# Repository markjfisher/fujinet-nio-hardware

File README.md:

# fujinet-nio-hardware
Hardware projects for NIO

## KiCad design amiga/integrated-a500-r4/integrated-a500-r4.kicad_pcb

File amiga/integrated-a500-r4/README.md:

Current integration checkpoint: [CadMust-Neo plan and compatibility findings](review/cadmust-integration/plan.md). Approved capacitor footprints and obsolete groups are now repaired; no optimisation or placement movement has run.

# A500 R4 — first physical placement candidate

R4 turns the protected R3 circuit into a **111 × 117 mm horizontal sidecar
placement**, with the female A500 socket at the right edge and an 18 mm
component-free band behind that edge (the socket solder lands are excepted). It is a new project;
released passive hardware and R0–R3 remain unchanged.

Placement preparation: [readiness report, exact bulk capacitors and lock classifications](review/placement-readiness/report.md). Q5 library warning is resolved; PCB positions/locks are unchanged.

Current status: [Phase 1 implementation and checks](review/component-optimisation/phase1-status.md).
Open the [native project](integrated-a500-r4.kicad_pro), [current schematic](review/schematic.pdf)
or [board and staging preview](phase1/board-and-staging.png). There are **199 fitted
components and four mounting holes**. New/repackaged components are staged outside
the preserved outline, awaiting placement. **There is no routed copper.** Earlier
placement pictures and review inventories are historical baseline artifacts.
USB main power is mandatory; the [implemented protection](review/component-optimisation/bus-output-disable-proposal.md)
uses a small current-limited host-interface supply and supervises all relevant rails.

The following table records the original placement basis; Phase 1 supersedes its
power/guard description and component counts.

| Requirement | Implementation | Evidence/check | Remaining decision or check |
| --- | --- | --- | --- |
| Direct horizontal A500 attachment | ED86BGFBK assembly footprint at right edge; board extends left | Original Matze Eagle package and supplied Gerbers; native check of all 86 pads | Tail-forming process, socket/body and case fit |
| Run / Flash RP / Flash ESP | Shared USB-C, two analog switches, cold mode jumper | Eight control combinations; exact native nets | Coupled USB routing and switched-circuit qualification |
| Independent recovery | Four physical BOOT/RESET buttons; RP SWD and ESP UART headers | Complete pin allocation and PCB pad coverage | Final button/header height and enclosure access |
| Power and Amiga-off isolation | USB-C >=1.5A source; protected input, reverse blocking; Amiga 5V sensed only | [Power calculation and assumptions](../integrated-a500-r3/power-review.md); 1.166A conditional input budget | Buck layout, effective capacitance, thermal/fault/current-downgrade behaviour |
| RP pins and bus safety | All 48 GPIO allocated; dedicated USB/QSPI/debug; LVC buffers and hardware interlocks | [Pin table](rp2350-pin-allocation.csv); 65,536 static and 65,536 sequential cases | PIO deadlines, propagation delay and active-bus validation |
| RP regulator placement | Six reference footprints and relative positions from Raspberry Pi's R4 design | Native geometric/net checks; source hash and MIT notice retained | Copper, ground return and regulator qualification |
| Physical layout | Four copper layers enabled; local bus/control bypass capacitors; antenna keepout on all copper | Native parity, DRC, pad mapping and visual inspection | Stackup, critical routing, ordinary routing, final BOM and DFM |

The electrical decisions remain in the [R3 power review](../integrated-a500-r3/power-review.md),
[R2 engineering](../integrated-a500-r2/engineering.md) and
[bus review](../integrated-a500-r3/bus-review.md). R4 changes footprint assignments
and makes the unused microSD detection contacts explicit; it does not change
the bus protocol or consume additional RP GPIO. Existing USB demonstrations
and passive logic-analyzer observations remain accepted.

See [mechanical/component evidence](implementation.md) and
[verification and outstanding findings](review/verification.md).
The circuit BOM is not yet an orderable manufacturing BOM. No fabrication
files, vendor upload, order, push or workspace submodule-pin change is included.

## Historical construction — do not rerun on the authoritative project

The scripts below reconstruct the obsolete baseline and would discard incremental
Phase 1 changes and manual placement. Native KiCad is now authoritative. The
[Phase 1 tooling](phase1/README.md) is a one-time migration record, not a board generator.

Source the workspace `scripts/env.sh`. Run `build.py`, `pcb_build.py`,
`finish_mcp.py` and `apply_bypass.py` with the pinned
`repos/fujinet-nio-hardware/.local-tools/kicad/venv/bin/python`.
Run the native checking/geometry scripts with system Python:

1. `make_footprints.py` constructs the A500 footprint through pcbnew. The six
   checked-in RP footprints are already present. To refresh those, download the
   cited official reference ZIP and pass its extracted directory to
   `import_rp_footprints.py`.
2. Register the project-local library using
   `uv run --with kiutils==1.4.8 python register_library.py`.
   This writes library configuration only, using its LibTable serializer.
3. `build.py`, then `check.py`: MCP schematic construction and independent
   native netlist/ERC/PDF export. `update_footprints.py` is an optional incremental
   property update, not required after a fresh build.
4. `pcb_build.py`: MCP board construction and constrained placement. Its
   `pending_approval` status is an internal routing checkpoint, not a request
   for another user permission.
5. `finish_native.py`, then `finish_mcp.py`: repair the documented tool export
   gaps, establish DFM targets and make the placement adjustments.
6. `plan_bypass.py`, then `apply_bypass.py`: calculate legal local bypass
   positions and apply them through MCP.
7. `fit_mechanics.py`, then `apply_mechanics.py`, then `reserve_connector.py`
   applies the owner-measured envelope without regenerating the board.
8. `plan_clusters.py`, then MCP `apply_clusters.py`, then native
   `create_groups.py`: place circuit cells, create named groups and move the
   two SD supply capacitors to the underside.
9. `plan_power_cell.py`, then MCP `apply_clusters.py power-cell-plan.json`:
   orient the buck cell and place its supply capacitors locally.
10. MCP `apply_clusters.py tidy-plan.json` applies the subsequent review
    adjustments. Then `plan_labels.py`, followed by MCP `apply_labels.py`: reserve consistent cell-label
    positions and apply visible 0.9 mm references. Run the planner immediately
    before the applicator; its update list is relative to the saved board.
11. `check.py`, `power_check.py`, `pcb_check.py`: independent final checks.
   `pcb_check.py` also exports native top and mirrored bottom placement SVGs. Raster preview uses
   CairoSVG; no image generation or hand-edited CAD is involved.

The actual saved candidate is the review artifact. These scripts are not a
fabrication pipeline. Do not run whole-board generation after adding routes:
it replaces the board. Do not run generic placement autofix: this pinned MCP
implementation does not respect footprint locks.

## Placement readability pass

All 192 references are visible, horizontal and use 0.9 mm lettering with
0.15 mm strokes. Repeated control IC/bypass pairs share a placement pattern
and label baseline. Native KiCad groups collect 183 components into 54 named
circuit groups; standalone connectors and mounting holes remain separate.
Groups support selecting related parts together; they do not enforce electrical
layout rules. The RP reference regulator geometry is preserved.

USB, CC, ESP, SD and regulator capacitors have explicit circuit owners rather
than proximity inferred from the shared supply net. C42/C43 are on the bottom
near the SD supply contact; allow underside component clearance in the housing.
The buck output capacitor is now beside its regulator and inductor. These are
placement improvements; copper loops, return paths and USB geometry still need
routing and verification. See the detailed verification record.

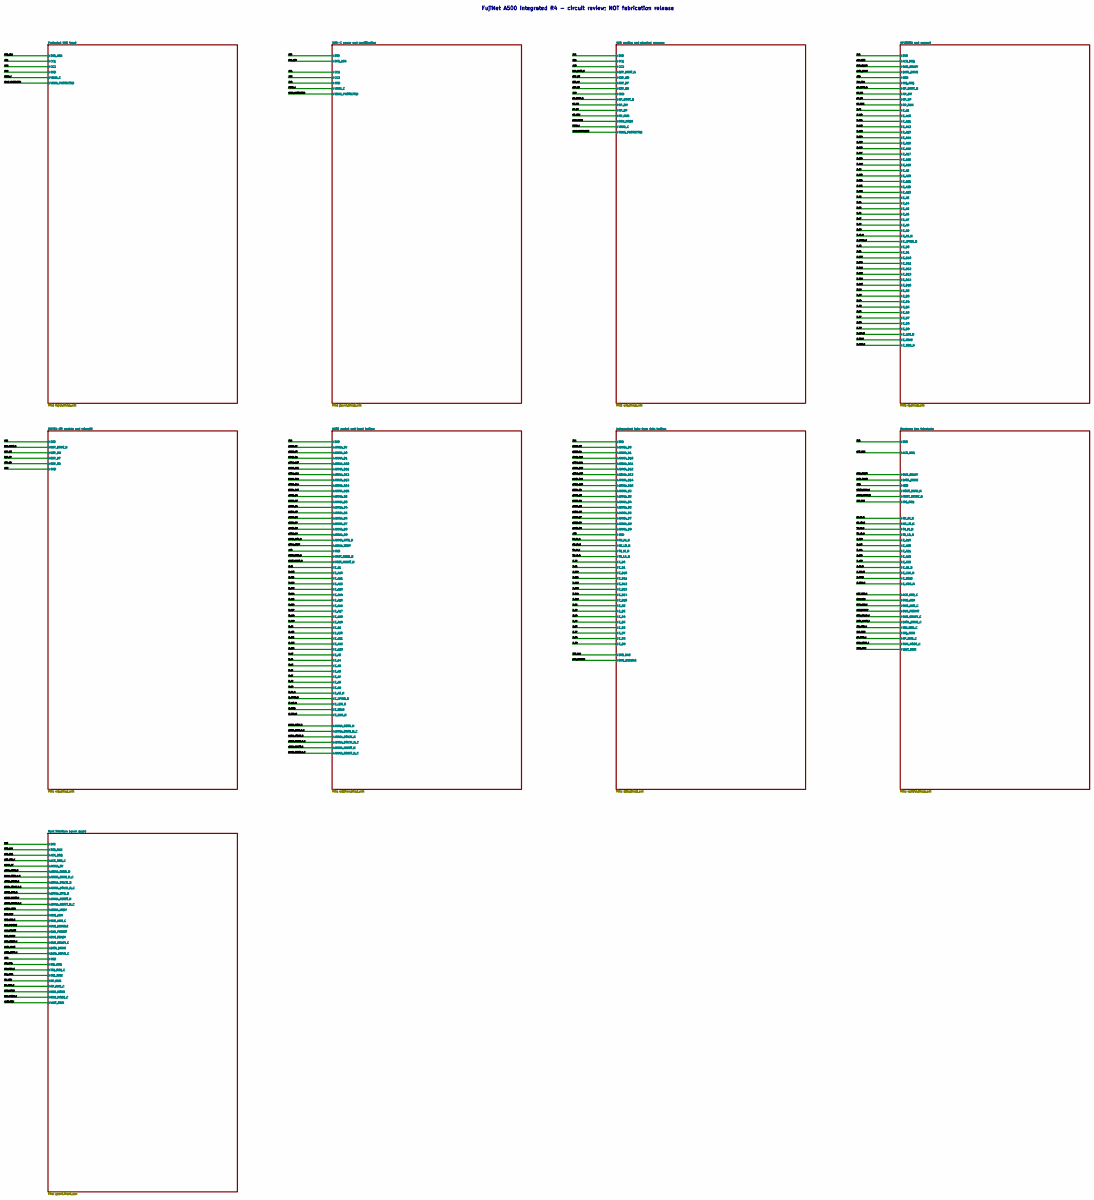
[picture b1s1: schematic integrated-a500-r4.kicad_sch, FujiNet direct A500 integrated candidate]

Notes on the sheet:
FujiNet A500 integrated R4 - circuit review; NOT fabrication release

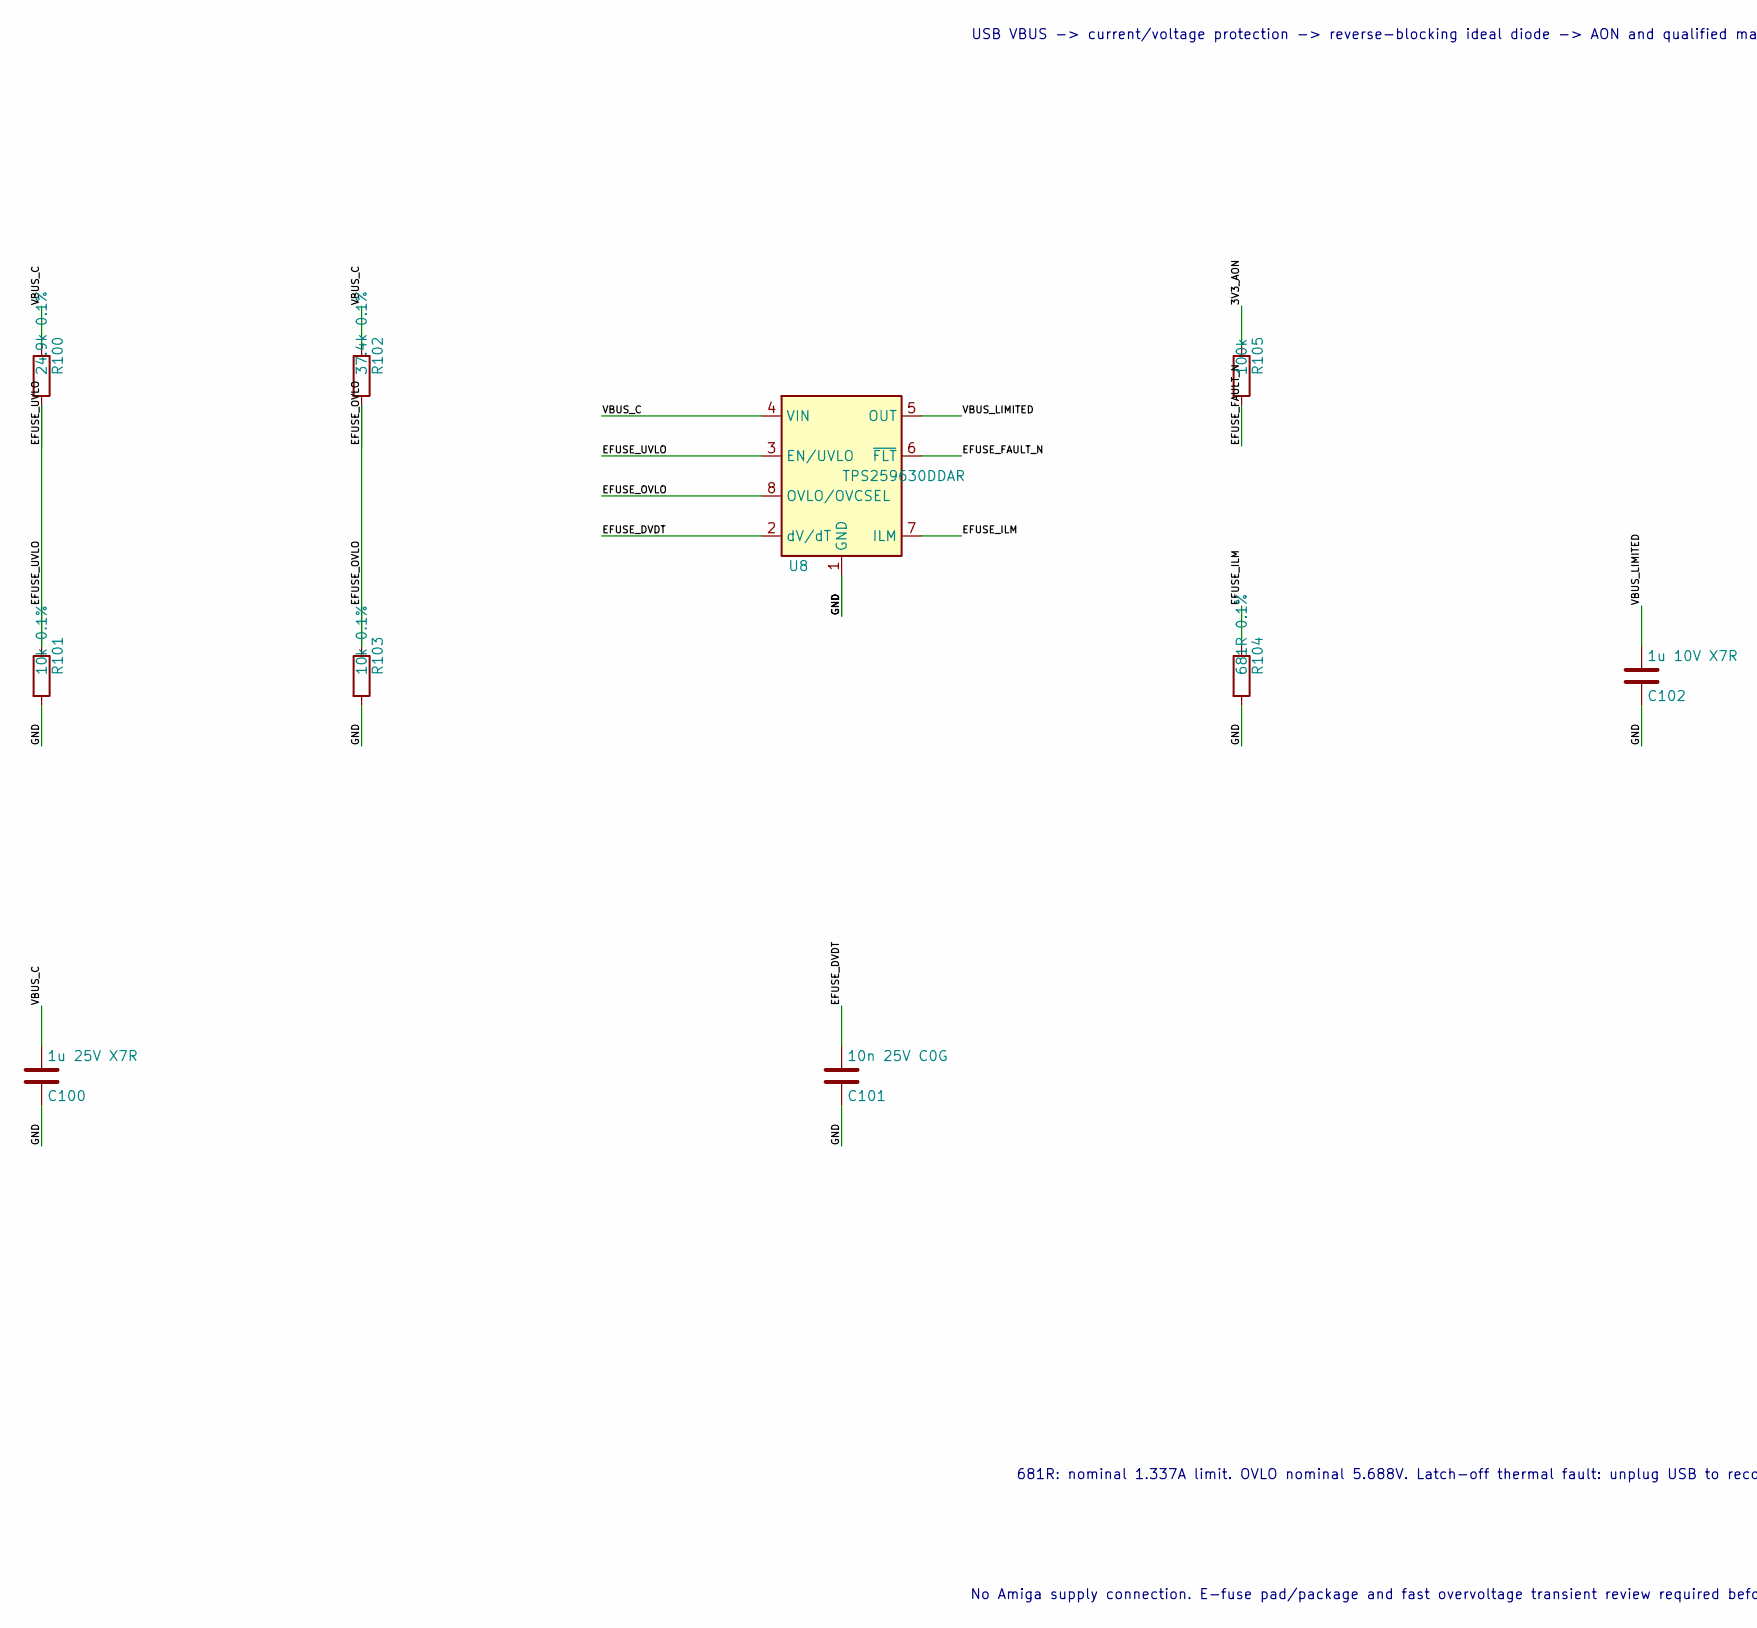
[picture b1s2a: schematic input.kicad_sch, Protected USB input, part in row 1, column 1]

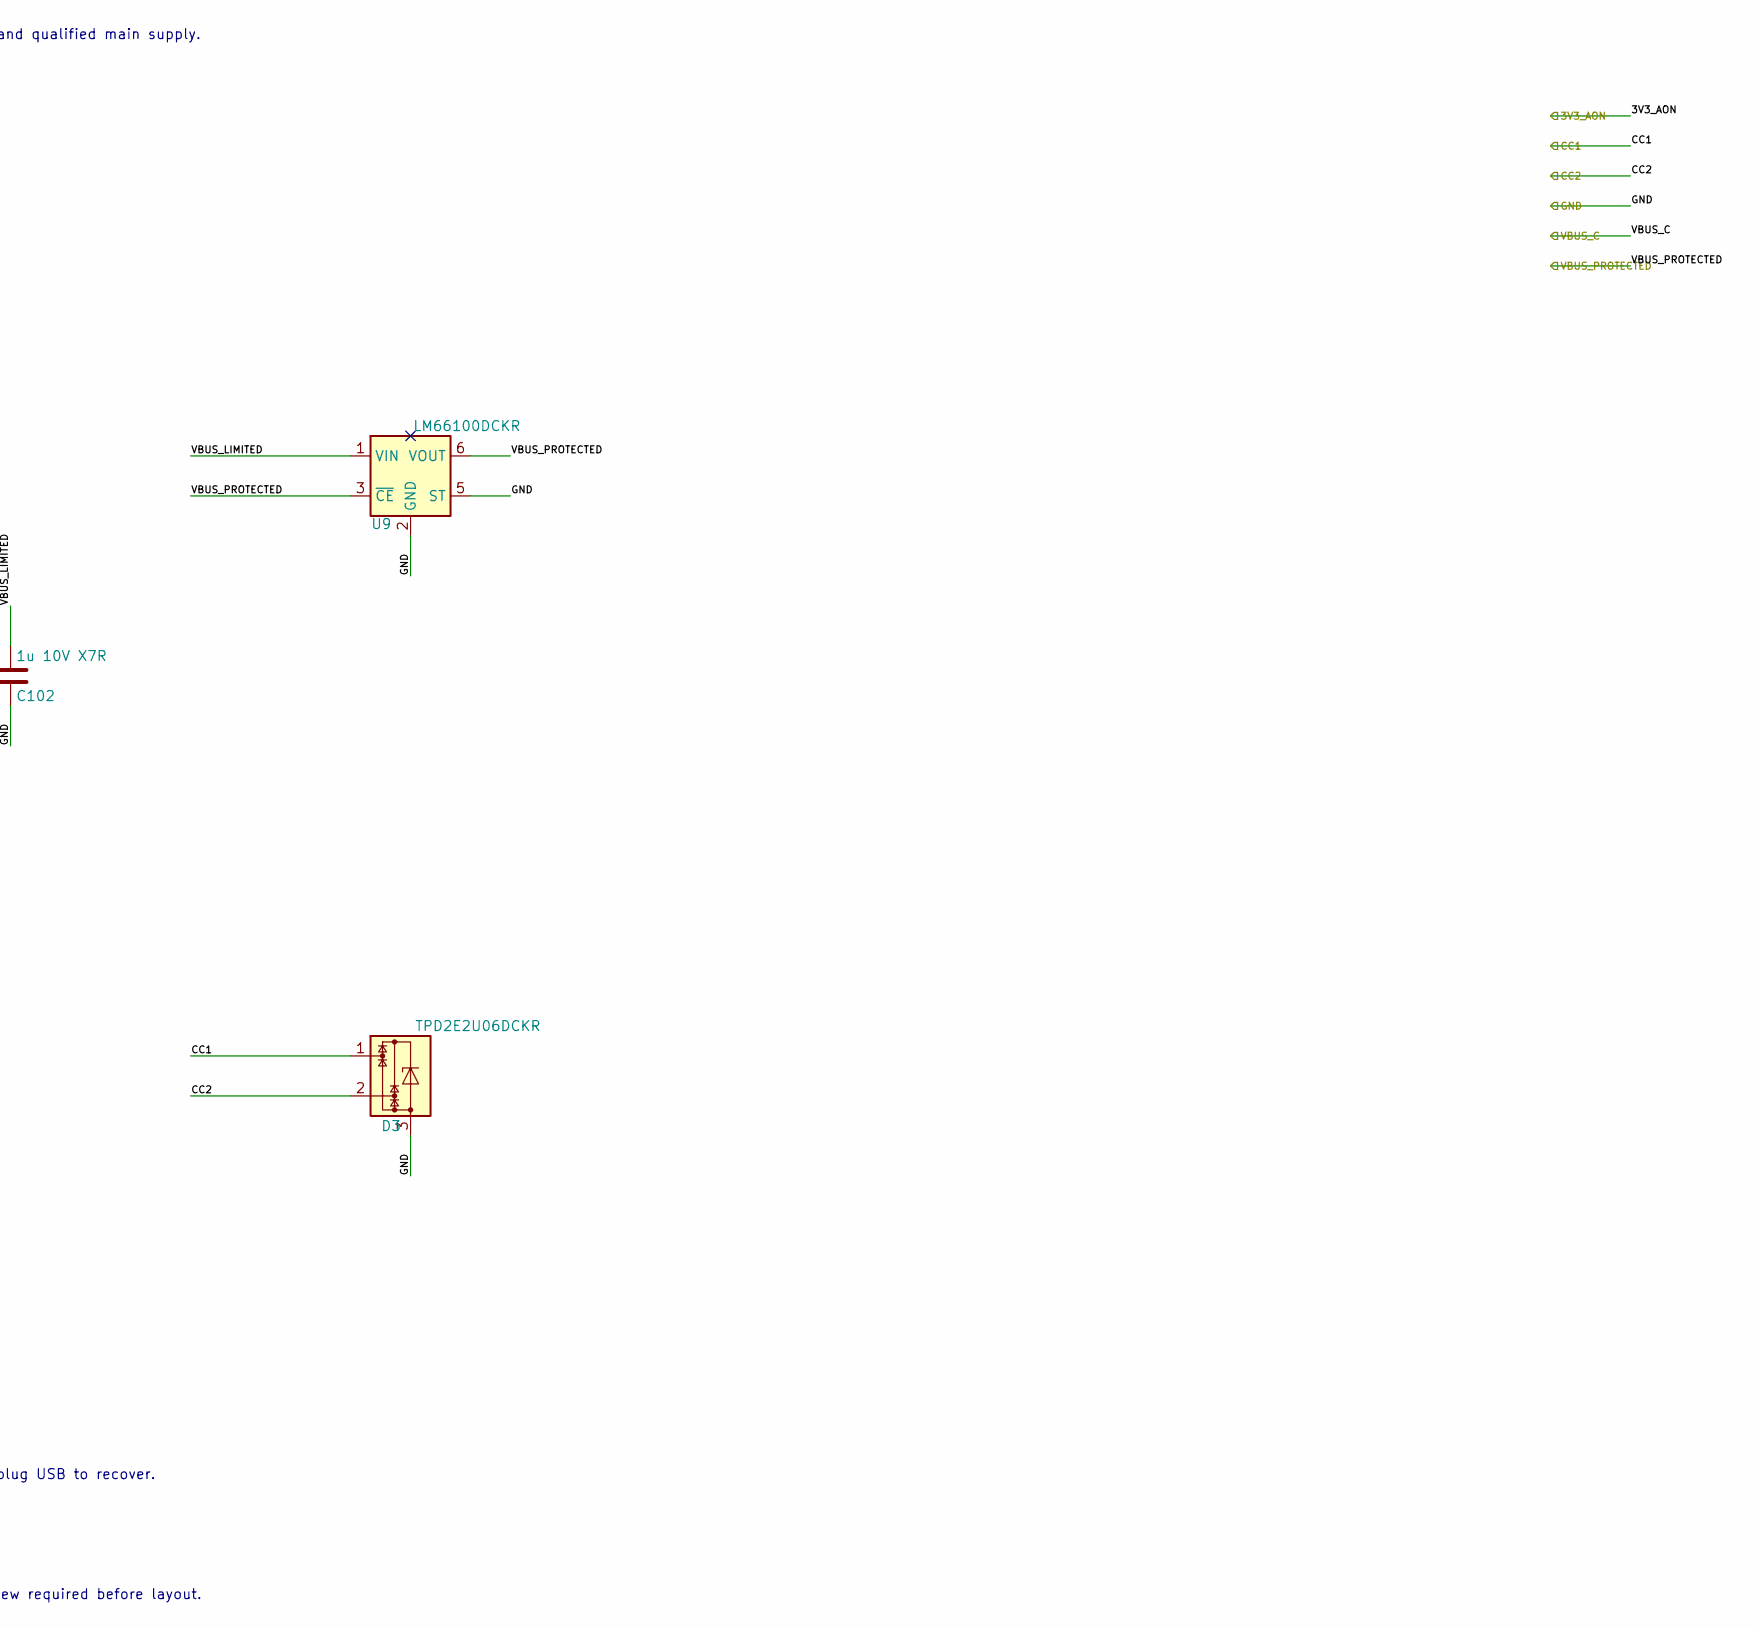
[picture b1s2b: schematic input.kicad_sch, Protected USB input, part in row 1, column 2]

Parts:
C100: 1u 25V X7R; C_0603_1608Metric
C101: 10n 25V C0G; C_0805_2012Metric
C102: 1u 10V X7R; C_0603_1608Metric
D3: TPD2E2U06DCKR; SOT-323_SC-70
R100: 24.9k 0.1%; R_0603_1608Metric
R101, R103: 10k 0.1%; R_0603_1608Metric
R102: 37.4k 0.1%; R_0603_1608Metric
R104: 681R 0.1%; R_0603_1608Metric
R105: 100k; R_0603_1608Metric
U8: TPS259630DDAR; TI_SO-PowerPAD-8
U9: LM66100DCKR; SOT-363_SC-70-6

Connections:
/3V3_AON: R105.1; also elsewhere on the board
/CC1: D3.1; also elsewhere on the board
/CC2: D3.2; also elsewhere on the board
/Protected USB input/EFUSE_DVDT: C101.1, U8.2 (dV/dT)
/Protected USB input/EFUSE_FAULT_N: R105.2, U8.6 (~FLT)
/Protected USB input/EFUSE_ILM: R104.1, U8.7 (ILM)
/Protected USB input/EFUSE_OVLO: R102.2, R103.1, U8.8 (OVLO/OVCSEL)
/Protected USB input/EFUSE_UVLO: R100.2, R101.1, U8.3 (EN/UVLO)
/Protected USB input/VBUS_LIMITED: C102.1, U8.5 (OUT), U9.1 (VIN)

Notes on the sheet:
USB VBUS -> current/voltage protection -> reverse-blocking ideal diode -> AON and qualified main supply.
681R: nominal 1.337A limit. OVLO nominal 5.688V. Latch-off thermal fault: unplug USB to recover.
No Amiga supply connection. E-fuse pad/package and fast overvoltage transient review required before layout.

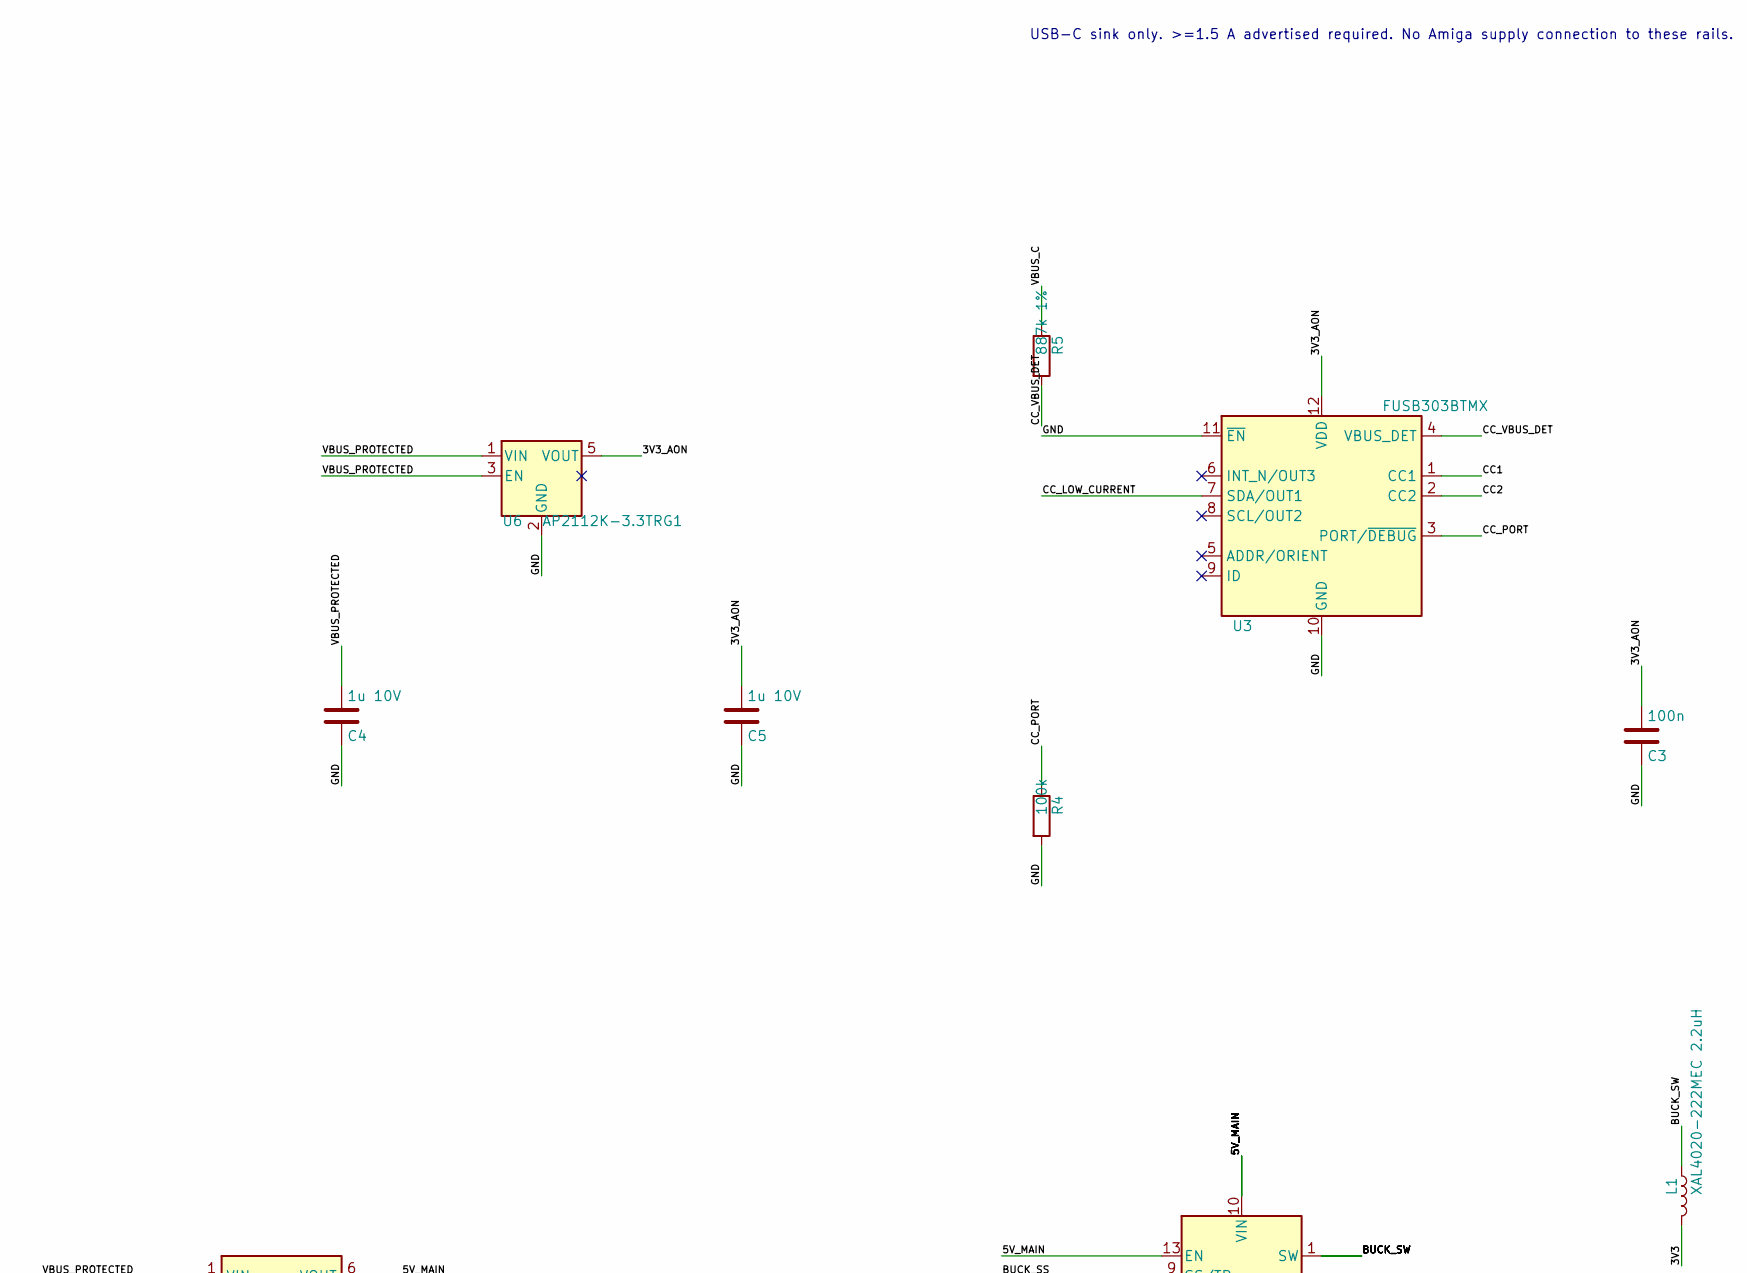
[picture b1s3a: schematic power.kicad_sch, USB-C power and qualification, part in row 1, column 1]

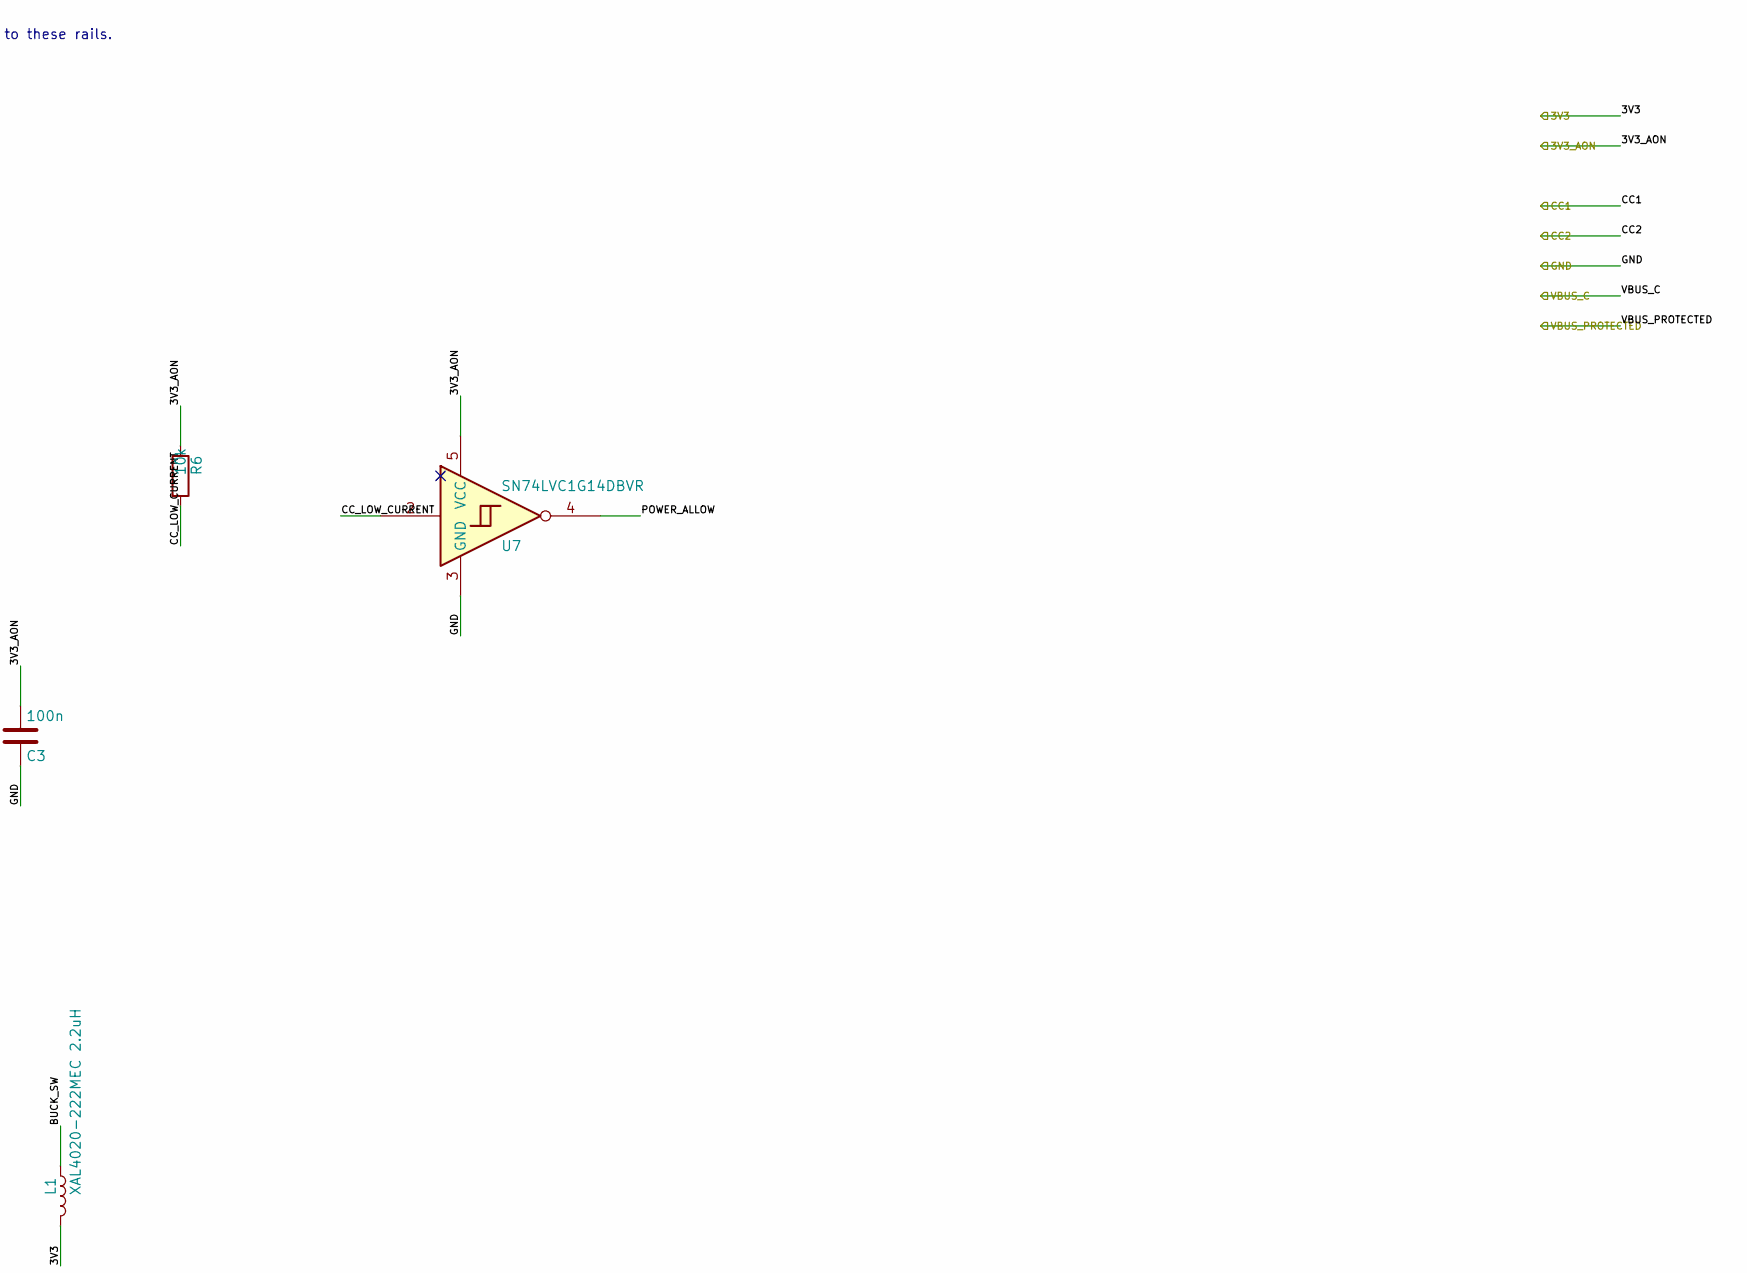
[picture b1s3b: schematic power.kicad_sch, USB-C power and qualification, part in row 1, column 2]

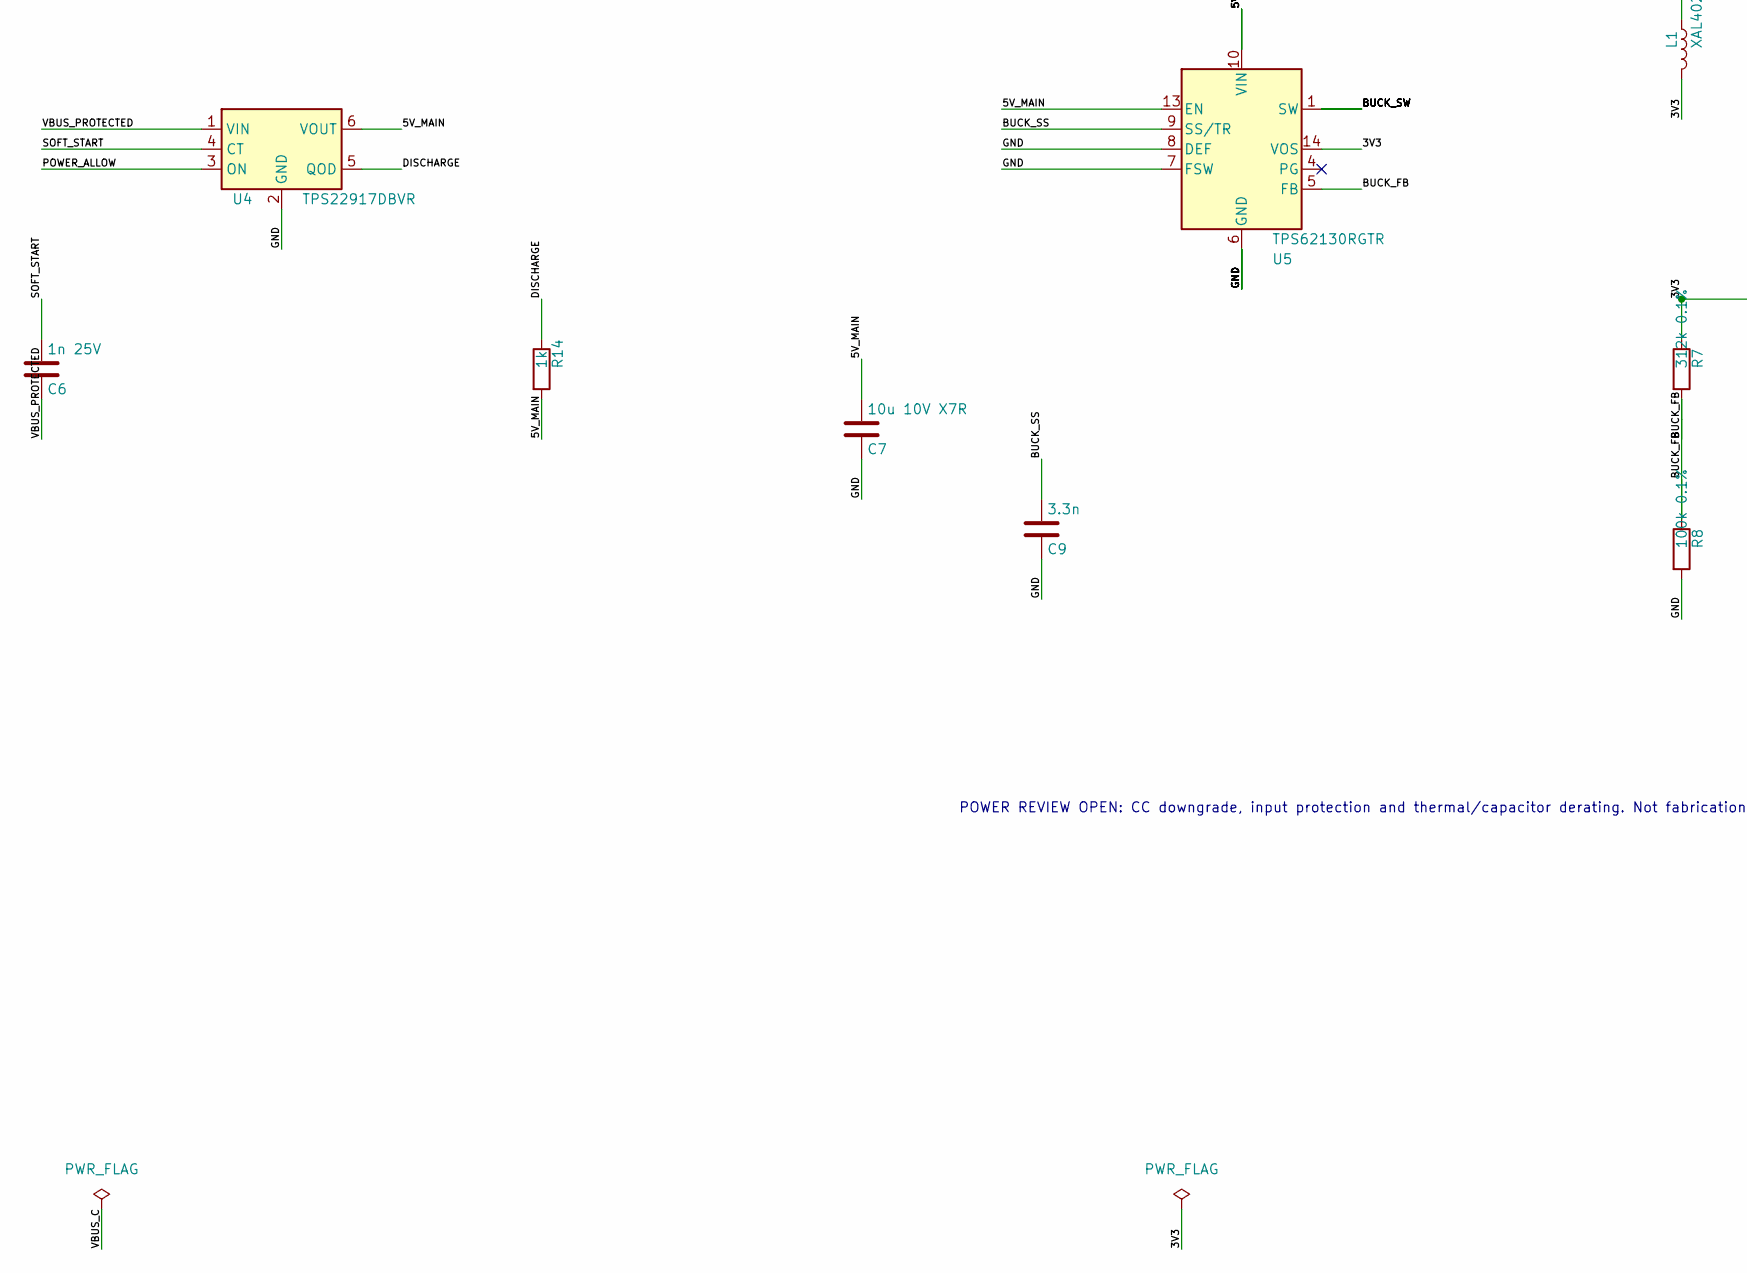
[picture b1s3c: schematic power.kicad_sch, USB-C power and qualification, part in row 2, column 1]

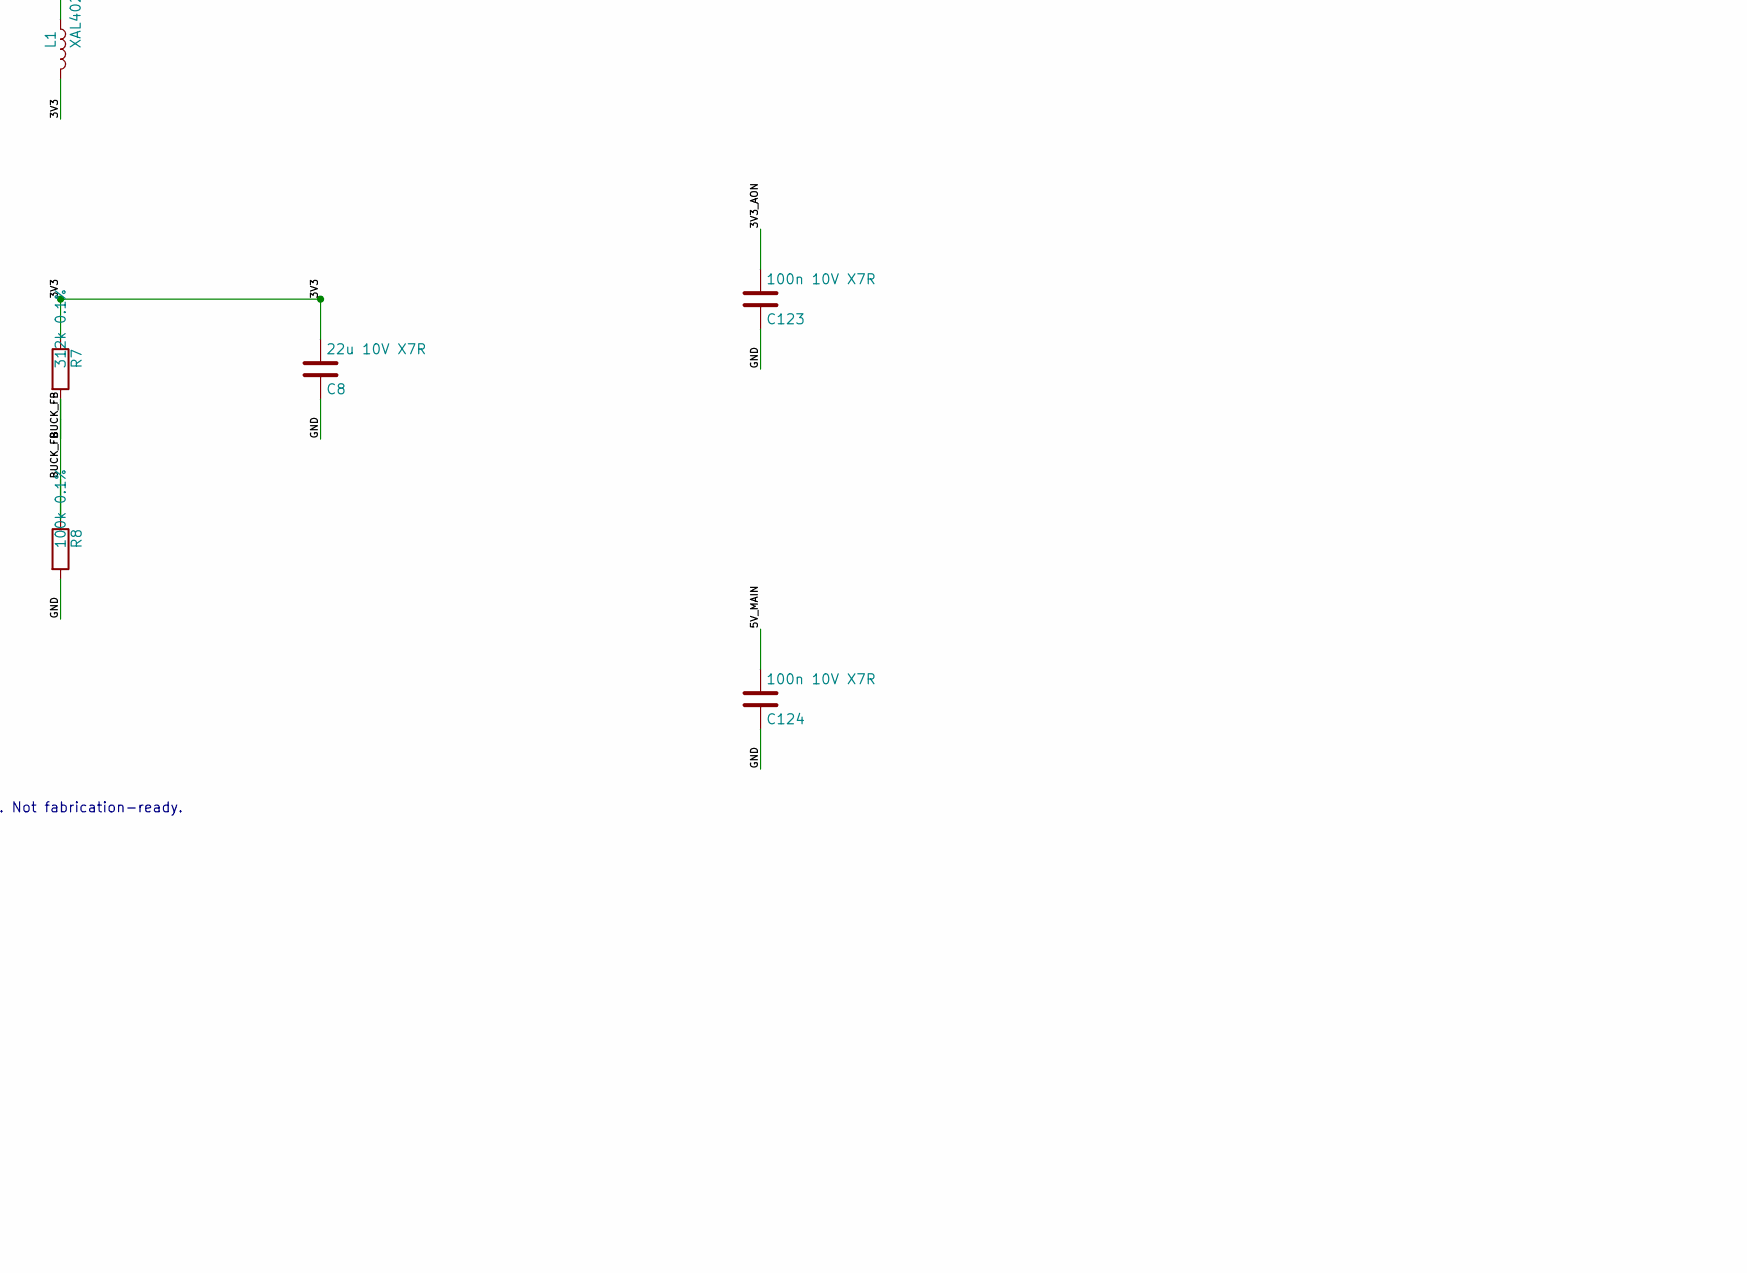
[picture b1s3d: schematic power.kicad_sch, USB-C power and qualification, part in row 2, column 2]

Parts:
C3: 100n; C_0603_1608Metric
C4, C5: 1u 10V; C_0603_1608Metric
C6: 1n 25V; C_0603_1608Metric
C7: 10u 10V X7R; C_1206_3216Metric
C8: 22u 10V X7R; C_1206_3216Metric
C9: 3.3n; C_0603_1608Metric
C123, C124: 100n 10V X7R; C_0603_1608Metric
L1: XAL4020-222MEC 2.2uH; L_Coilcraft_XAL4020-XXX
R4: 100k; R_0603_1608Metric
R5: 887k 1%; R_0603_1608Metric
R6: 10k; R_0603_1608Metric
R7: 312k 0.1%; R_0603_1608Metric
R8: 100k 0.1%; R_0603_1608Metric
R14: 1k; R_0603_1608Metric
U3: FUSB303BTMX; Texas_X2QFN-12_1.6x1.6mm_P0.4mm
U4: TPS22917DBVR; SOT-23-6
U5: TPS62130RGTR; VQFN-16-1EP_3x3mm_P0.5mm_EP1.68x1.68mm_ThermalVias
U6: AP2112K-3.3TRG1; SOT-23-5
U7: SN74LVC1G14DBVR; SOT-23-5

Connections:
/3V3: C8.1, L1.2, R7.1, U5.14 (VOS); also elsewhere on the board
/3V3_AON: C3.1, C5.1, C123.1, R6.1, U3.12 (VDD), U6.5 (VOUT), U7.5 (VCC); also elsewhere on the board
/CC1: U3.1 (CC1); also elsewhere on the board
/CC2: U3.2 (CC2); also elsewhere on the board
/USB-C power and qualification/5V_MAIN: C7.1, C124.1, R14.2, U4.6 (VOUT), U5.10 (VIN), U5.11 (VIN), U5.12 (VIN), U5.13 (EN)
/USB-C power and qualification/BUCK_FB: R7.2, R8.1, U5.5 (FB)
/USB-C power and qualification/BUCK_SS: C9.1, U5.9 (SS/TR)
/USB-C power and qualification/BUCK_SW: L1.1, U5.1 (SW), U5.2 (SW), U5.3 (SW)
/USB-C power and qualification/CC_LOW_CURRENT: R6.2, U3.7 (SDA/OUT1), U7.2
/USB-C power and qualification/CC_PORT: R4.1, U3.3 (PORT/~DEBUG)
/USB-C power and qualification/CC_VBUS_DET: R5.2, U3.4 (VBUS_DET)
/USB-C power and qualification/DISCHARGE: R14.1, U4.5 (QOD)
/USB-C power and qualification/POWER_ALLOW: U4.3 (ON), U7.4
/USB-C power and qualification/SOFT_START: C6.1, U4.4 (CT)

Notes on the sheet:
USB-C sink only. >=1.5 A advertised required. No Amiga supply connection to these rails.
POWER REVIEW OPEN: CC downgrade, input protection and thermal/capacitor derating. Not fabrication-ready.
